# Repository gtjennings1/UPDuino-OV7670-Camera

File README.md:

# UPDuino-OV7670-Camera
Design to connect Lattice Ultraplus FPGA to OV7670 Camera Module

UPDuino is an ultra low cost FPGA development and prototyping board.  The OV7670 Camera Module is an ultra low cost VGA camera module traditionally used for maker projects.  The UPDuino OV7670 Camera Module Adapter Board connects a OV7670 camera module to a UPDuino v2.0 board.  This user guide describes the hardware and software necessary to connect the OV7670 Camera module and an Arduino to a UPDuino board and stream image data from the Ultraplus FPGA frame buffer to a computer via UART.  The image data can then be copied into a file and be viewed as a bitmap.

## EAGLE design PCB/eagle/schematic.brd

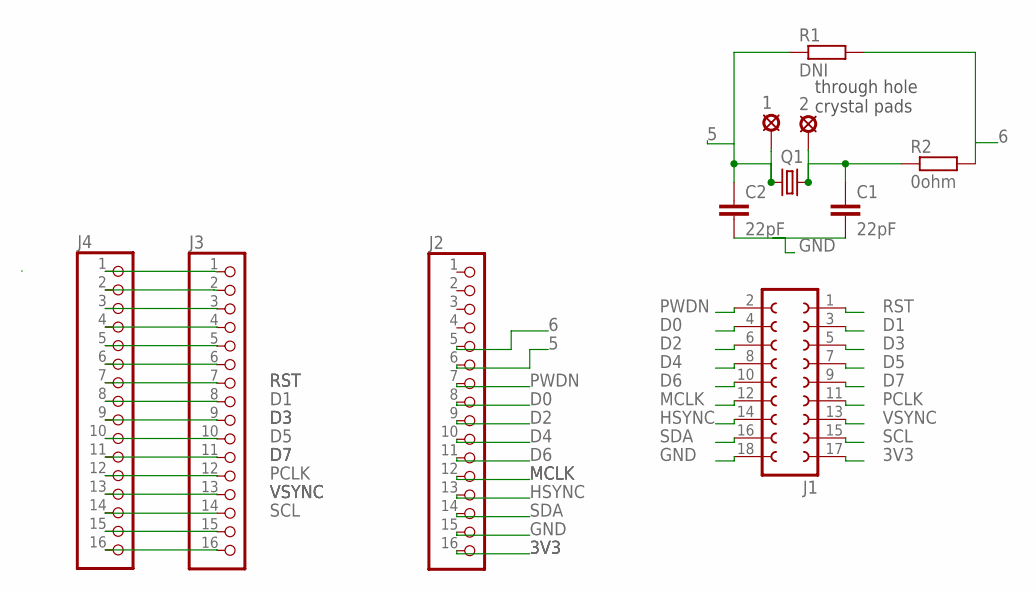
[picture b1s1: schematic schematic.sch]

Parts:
1, 2: LSP10
C1, C2: 22pF; C0603
J1: FE09-2
J2, J3, J4: PINHD-1X16; 1X16
Q1: CRYSTALHC49UP; HC49UP
R1: DNI; R0603
R2: 0ohm; R0603

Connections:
3V3: J1.17, J2.16
5: 1.MP, C2.1, J2.6, Q1.1, R1.1
6: J2.5, R1.2, R2.2
D0: J1.4, J2.8
D1: J1.3, J3.8, J4.8
D2: J1.6, J2.9
D3: J1.5, J3.9, J4.9
D4: J1.8, J2.10
D5: J1.7, J3.10, J4.10
D6: J1.10, J2.11
D7: J1.9, J3.11, J4.11
GND: C1.2, C2.2, J1.18, J2.15
HSYNC: J1.14, J2.13
MCLK: J1.12, J2.12
unnamed: J3.1, J4.1
unnamed: J3.2, J4.2
unnamed: J3.3, J4.3
unnamed: J3.5, J4.5
unnamed: J3.6, J4.6
unnamed: J3.4, J4.4
unnamed: 2.MP, C1.1, Q1.2, R2.1
unnamed: J3.15, J4.15
unnamed: J3.16, J4.16
PCLK: J1.11, J3.12, J4.12
PWDN: J1.2, J2.7
RST: J1.1, J3.7, J4.7
SCL: J1.15, J3.14, J4.14
SDA: J1.16, J2.14
VSYNC: J1.13, J3.13, J4.13

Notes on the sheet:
through hole crystal pads

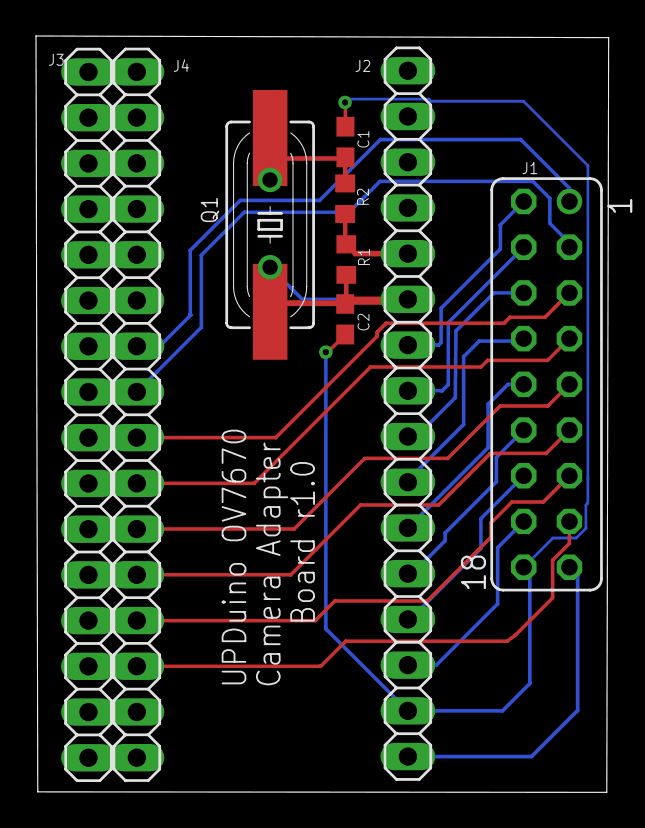
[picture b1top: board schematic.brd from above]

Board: 2 copper layers, 31.8 x 42.0 mm, 11 parts (0 on the bottom side), 29 nets.

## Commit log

2018-02-07 PCB files added
